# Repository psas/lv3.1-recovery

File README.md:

# LV-3.1 Recovery Repository

The LV-3.1 Electromechanical Recovery System (ERS) is a fully-resettable recovery system for the [PSAS](http://psas.pdx.edu/) Launch Vehicle v 3.1 (LV-3.1). Each ERS "unit" releases a single parachute. The top unit deploys our ballute test parachute that's in the nose cone, the next ERS unit releases a standard drogue, and the final ERS unit releases the main parachute.

## Mechanical CAD
All mechanical CAD has been moved to OnShape and can be found [here](https://cad.onshape.com/documents/03e169a7501c9614bcd8fe34/w/d2206dc55680e29e4d8f6e15/e/43f9d4697ebc459acca1436a).

## Control System

In this Git repo is a PCB with STM32F091 microcontroller that controls the system. See the ControlSystem directory.

## Testing and Analysis

The ERS system will be tested by dropping it from a helicopter over a field. Many parameters must be considered for this test including wind speed, altitude, field size, parachute drag coefficients, and parachute release timing. Analysis of drop test dispersal patterns based on fixing some parameters and simulating variation in others enables us to choose an appropriate drop site and drop parameters. Analysis notebooks can by found in the /analysis directory.

* [Parent Directory](https://github.com/psas/lv3.1-recovery/tree/master/Analysis)
* [Primary mission analysis document](https://github.com/psas/lv3.1-recovery/blob/master/Analysis/Mission_Analysis.ipynb)
* [Jupyter Notebook to run simulations](https://github.com/psas/lv3.1-recovery/blob/master/Analysis/drop_test_simulator.ipynb)

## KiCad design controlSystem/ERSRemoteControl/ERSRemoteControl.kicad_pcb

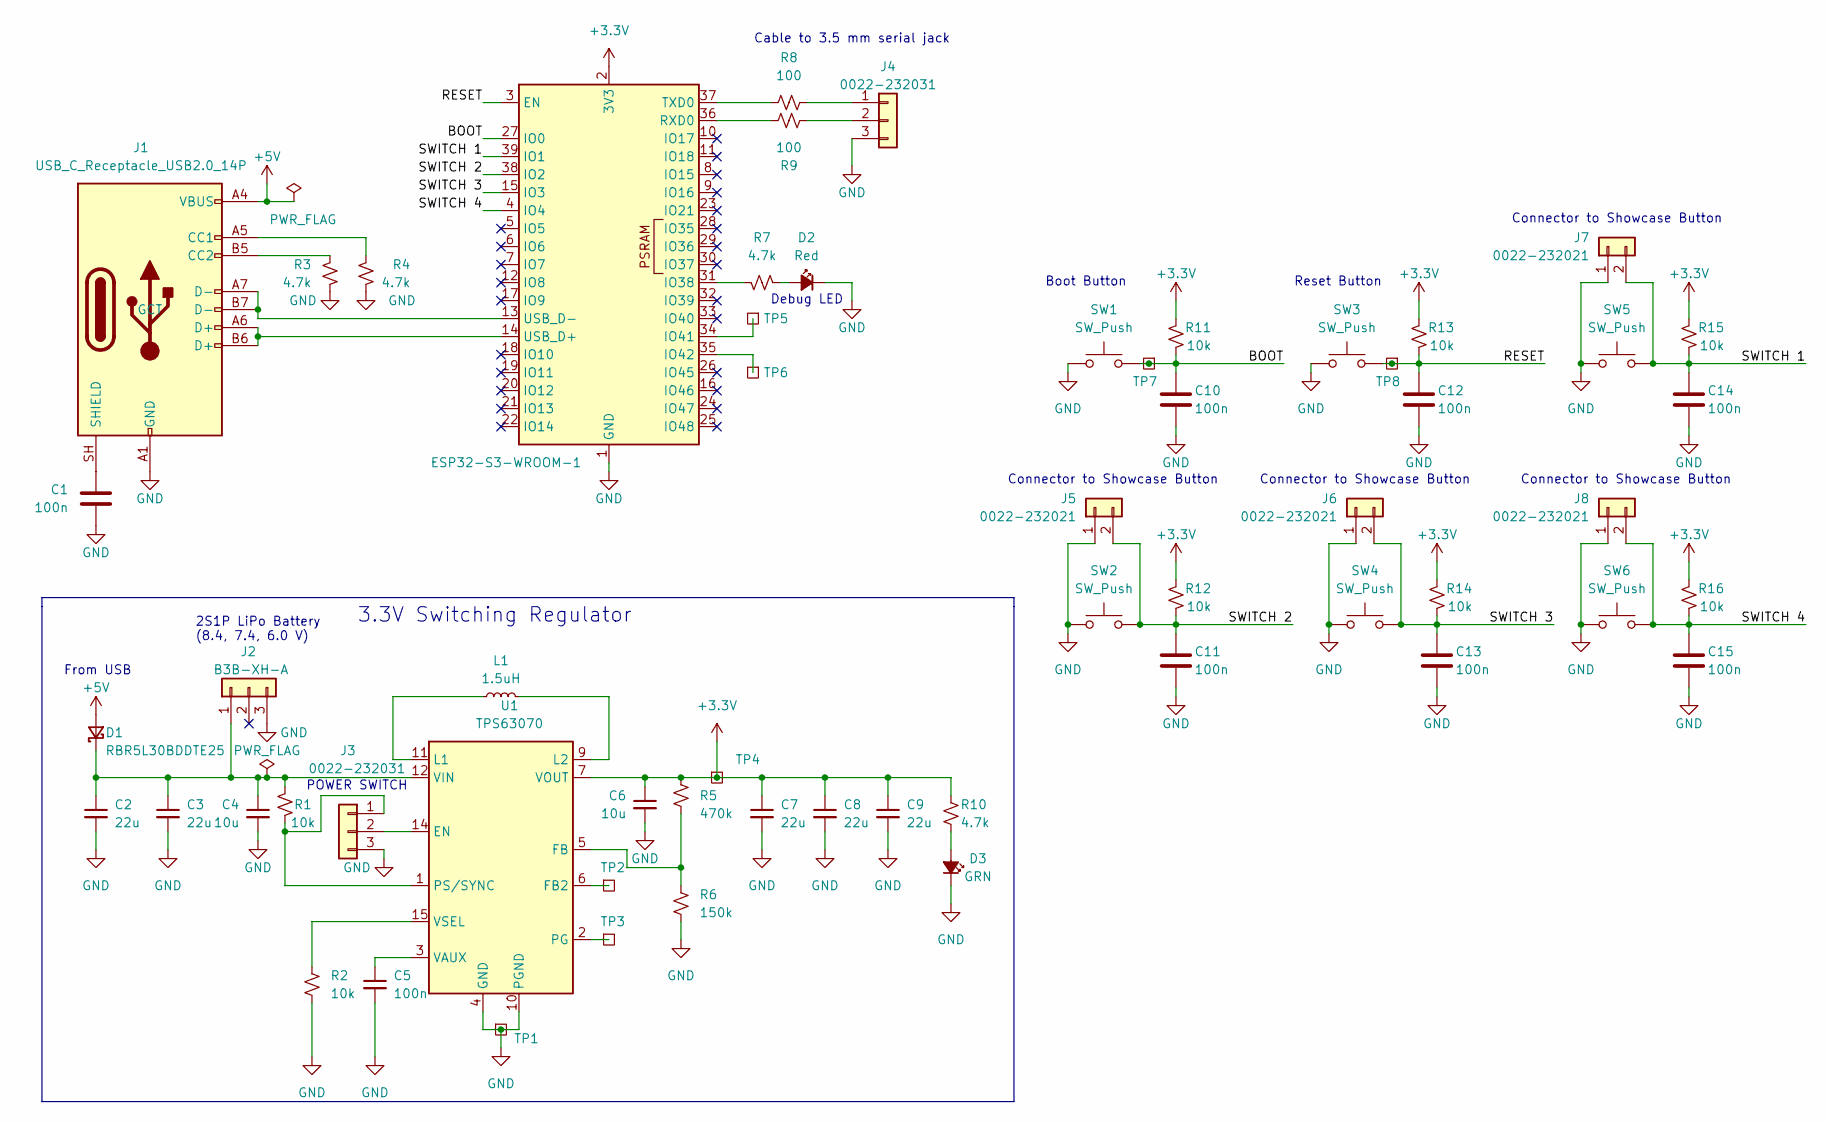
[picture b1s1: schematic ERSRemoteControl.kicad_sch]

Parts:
C1, C5, C10, C11, C12, C13, C14, C15: 100n; C_0603_1608Metric; MPN CL10B104KB8WPNC
C2, C3, C7, C8, C9: 22u; C_0805_2012Metric; MPN GRT21BC81C226ME13L
C4, C6: 10u; C_0805_2012Metric; MPN GRT21BC71E106KE13K
D1: RBR5L30BDDTE25; D_SMA; MPN RBR5L30BDDTE25
D2: Red; LED_0603_1608Metric; MPN 150060SS75000
D3: GRN; LED_0603_1608Metric; MPN 150060GS75000
J1: USB_C_Receptacle_USB2.0_14P; USB_C_Receptacle_Palconn_UTC16-G; MPN USB4105-GF-A
J2: B3B-XH-A; JST_XH_B3B-XH-A_1x03_P2.50mm_Vertical; MPN B3B-XH-A
J3, J4: 0022-232031; Molex_KK-254_AE-6410-03A_1x03_P2.54mm_Vertical; MPN 22232031
J5, J6, J7, J8: 0022-232021; Molex_KK-254_AE-6410-02A_1x02_P2.54mm_Vertical; MPN 22232021
L1: 1.5uH; L_Vishay_IHLP-2020; MPN IHLP2020CZER1R5M11
R1, R2, R11, R12, R13, R14, R15, R16: 10k; R_0603_1608Metric; MPN RC0603FR-0710KL
R3, R4, R7, R10: 4.7k; R_0603_1608Metric; MPN RMCF0603FT4K70
R5: 470k; R_0603_1608Metric; MPN RMCF0603FT470K
R6: 150k; R_0603_1608Metric; MPN RC0603FR-07150KL
R8, R9: 100; R_0603_1608Metric; MPN RC0603FR-07100RL
SW1, SW2, SW3, SW4, SW5, SW6: SW_Push; SW_PUSH_6mm; MPN B3F-1000
TP1, TP2, TP3, TP4, TP5, TP6, TP7, TP8: Test-Point; TP-through-hole-1X01
U1: TPS63070; U-TI-TPS63070; MPN TPS63070RNMR
U2: ESP32-S3-WROOM-1; MPN ESP32-S3-WROOM-1-N4R8

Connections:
+3.3V: C6.1, C7.1, C8.1, C9.1, R5.1, R10.1, R11.1, R12.1, R13.1, R14.1, R15.1, R16.1, TP4.1 (1_1), U1.7 (VOUT), U1.8 (VOUT), U1.TIE2 (VOUT), U2.2 (3V3)
+5V: D1.2 (A), J1.A4 (VBUS), J1.A9 (VBUS), J1.B4 (VBUS), J1.B9 (VBUS)
/BOOT: C10.1, R11.2, SW1.1, TP7.1 (1_1), U2.27 (IO0)
/RESET: C12.1, R13.2, SW3.1, TP8.1 (1_1), U2.3 (EN)
/SWITCH 1: C14.1, J7.2, R15.2, SW5.1, U2.39 (IO1)
/SWITCH 2: C11.1, J5.2, R12.2, SW2.1, U2.38 (IO2)
/SWITCH 3: C13.1, J6.2, R14.2, SW4.1, U2.15 (IO3)
/SWITCH 4: C15.1, J8.2, R16.2, SW6.1, U2.4 (IO4)
GND: C1.2, C2.2, C3.2, C4.2, C5.2, C6.2, C7.2, C8.2, C9.2, C10.2, C11.2, C12.2, C13.2, C14.2, C15.2, D2.1 (K), D3.1 (K), J1.A1 (GND), J1.A12 (GND), J1.B1 (GND), J1.B12 (GND), J2.3, J3.3, J4.3, J5.1, J6.1, J7.1, J8.1, R2.2, R3.2, R4.2, R6.2, SW1.2, SW2.2, SW3.2, SW4.2, SW5.2, SW6.2, TP1.1 (1_1), U1.4 (GND), U1.10 (PGND), U2.1 (GND), U2.40 (GND), U2.41 (GND)
unnamed: C2.1, C3.1, C4.1, D1.1 (K), J2.1, R1.2, U1.12 (VIN), U1.13 (VIN), U1.TIE1 (VIN)
unnamed: D2.2 (A), R7.1
unnamed: D3.2 (A), R10.2
unnamed: J1.A5 (CC1), R4.1
unnamed: J1.B5 (CC2), R3.1
unnamed: C1.1, J1.SH (SHIELD)
unnamed: J3.1, R1.1, U1.1 (PS/SYNC)
unnamed: J3.2, U1.14 (EN)
unnamed: J4.1, R8.2
unnamed: J4.2, R9.1
unnamed: TP2.1 (1_1), U1.6 (FB2)
unnamed: R5.2, R6.1, U1.5 (FB)
unnamed: L1.1, U1.11 (L1)
unnamed: L1.2, U1.9 (L2)
unnamed: TP3.1 (1_1), U1.2 (PG)
unnamed: C5.1, U1.3 (VAUX)
unnamed: R2.1, U1.15 (VSEL)
unnamed: R7.2, U2.31 (IO38)
unnamed: TP5.1 (1_1), U2.34 (IO41)
unnamed: TP6.1 (1_1), U2.35 (IO42)
unnamed: R9.2, U2.36 (RXD0)
unnamed: R8.1, U2.37 (TXD0)
unnamed: J1.A6 (D+), J1.B6 (D+), U2.14 (USB_D+)
unnamed: J1.A7 (D-), J1.B7 (D-), U2.13 (USB_D-)

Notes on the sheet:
Reset Button
3.3V Switching Regulator
2S1P LiPo Battery (8.4, 7.4, 6.0 V)
Connector to Showcase Button
Boot Button
Cable to 3.5 mm serial jack
From USB
POWER SWITCH
Debug LED

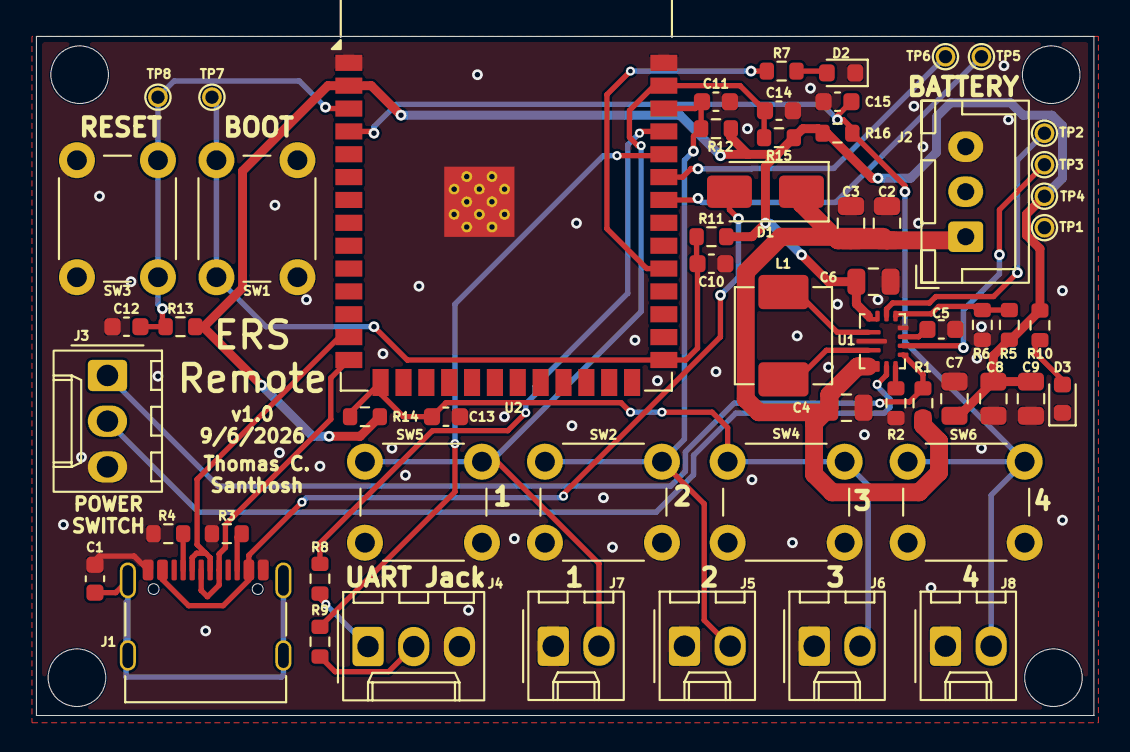
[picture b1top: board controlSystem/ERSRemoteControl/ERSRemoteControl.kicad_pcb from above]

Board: 2 copper layers, 58.8 x 37.7 mm, 59 parts (0 on the bottom side), 33 nets.

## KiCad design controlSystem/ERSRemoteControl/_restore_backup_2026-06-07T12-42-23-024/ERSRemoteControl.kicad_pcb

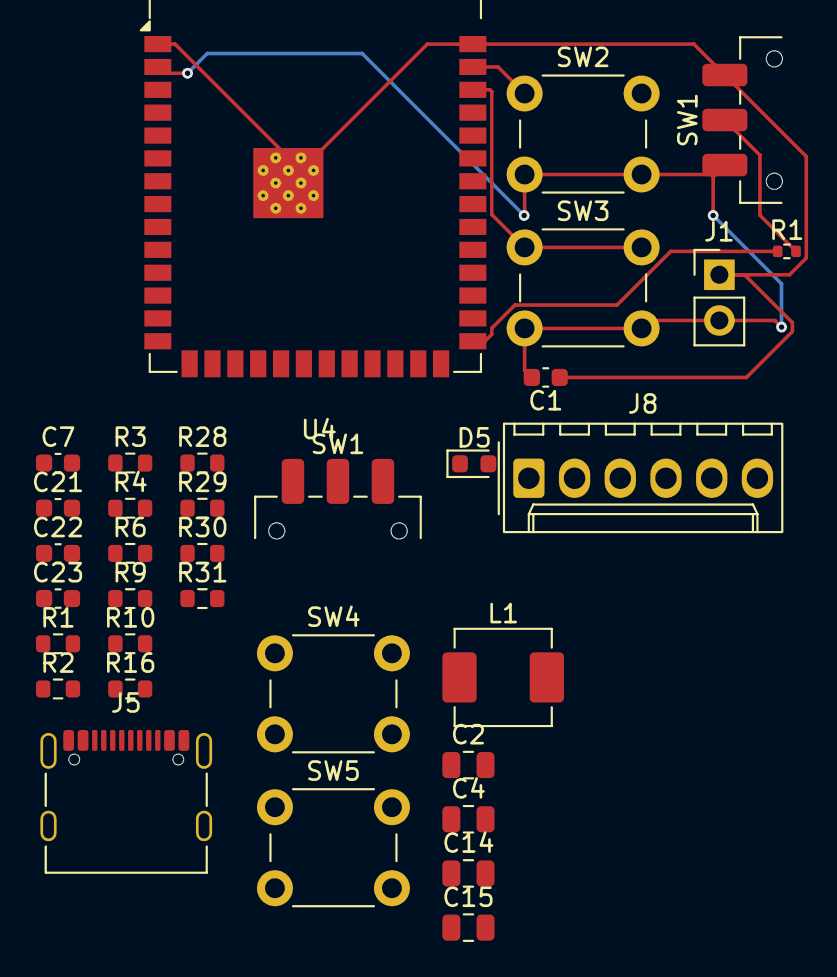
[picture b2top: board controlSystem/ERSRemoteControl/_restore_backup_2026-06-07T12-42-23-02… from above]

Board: 2 copper layers, 34 parts (0 on the bottom side), 17 nets.

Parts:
C1, C7, C21, C22, C23: 100n; C_0603_1608Metric
C2, C4, C14, C15: 22u; C_0805_2012Metric
D5: GRN; LED_0603_1608Metric
J1: Conn_01x02_Socket; PinHeader_1x02_P2.54mm_Vertical
J5: USB_C_Receptacle_USB2.0_14P; USB_C_Receptacle_Palconn_UTC16-G
J8: 00222-32051; Molex_KK-254_AE-6410-06A_1x06_P2.54mm_Vertical
L1: 1.5uH; L_Vishay_IHLP-2020
R1: R_US; R_0402_1005Metric
R1#2, R2, R3: 220; R_0603_1608Metric
R4, R6, R30, R31: 10k; R_0603_1608Metric
R9: 470k; R_0603_1608Metric
R10: 150k; R_0603_1608Metric
R16, R28, R29: 4.7k; R_0603_1608Metric
SW1, SW1#2: SW_SPDT; SW_SPDT_CK_JS102011SAQN
SW2, SW3, SW4, SW5: SW_Push; SW_PUSH_6mm
U4: ESP32-S3-WROOM-1

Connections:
+3.3V: C1.1, C14.1, C15.1, J1.2, R9.1, R16.1, R30.1, R31.1, SW1.1 (A), SW1#2.1 (A), SW2.2, SW3.2, U4.2 (3V3)
+5V: C2.1, C4.1, J5.A4 (VBUS), J5.A9 (VBUS), J5.B4 (VBUS), J5.B9 (VBUS), R6.1
GND: C1.2, C2.2, C4.2, C7.2, C14.2, C15.2, C21.2, C22.2, C23.2, D5.1 (K), J1.1, J5.A1 (GND), J5.A12 (GND), J5.B1 (GND), J5.B12 (GND), R4.2, R10.2, R28.2, R29.2, SW1.3 (C), SW1#2.3 (C), SW4.2, SW5.2, U4.1 (GND), U4.40 (GND), U4.41 (GND)
unnamed: D5.2 (A), R16.2
unnamed: J5.A5 (CC1), R29.1
unnamed: J5.B5 (CC2), R28.1
unnamed: R2.2, SW2.1
unnamed: R3.2, SW3.1
unnamed: R1.2, R1#2.2, SW1.2 (B), SW1#2.2 (B)
unnamed: R9.2, R10.1
unnamed: C22.1, R30.2, SW4.1, U4.3 (EN)
unnamed: C23.1, R1.1, R31.2, SW5.1, U4.27 (IO0)
unnamed: R2.1, U4.39 (IO1)
unnamed: R3.1, U4.38 (IO2)
unnamed: R1#2.1, U4.15 (IO3)
unnamed: J5.A6 (D+), J5.B6 (D+), U4.14 (USB_D+)
unnamed: J5.A7 (D-), J5.B7 (D-), U4.13 (USB_D-)

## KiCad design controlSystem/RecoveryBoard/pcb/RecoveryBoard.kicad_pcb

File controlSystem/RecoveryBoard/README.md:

# Electromechanical Recovery System (ERS) v4.0 Controller Board 

## General information
This board controls the ERS v4 modules in LV3.1 and hopefully eventually in LV4.

Full documentation can be found [here](https://docs.google.com/document/d/1TOoC-d3vpsw2uvtvazEmFV9_g59nFPVRWKC9Ye5qgKw/edit?usp=sharing)

## Firmware

The firmware is written in C and runs on top of ChibiOS, a small RTOS. See the "firmware" directory. The [oresat-firmware](https://github.com/oresat/oresat-firmware) repository has instructions on how to get started on the tool chain.

## License

All materials in this repo are copyright Portland State Aerospace Society and are licensed under the CERN Open Hardware Licence Version 2 -
Strongly Reciprocal (CERN-OHL-S v2), or any later version. A copy of the license is located in [here](LICENSE.md).

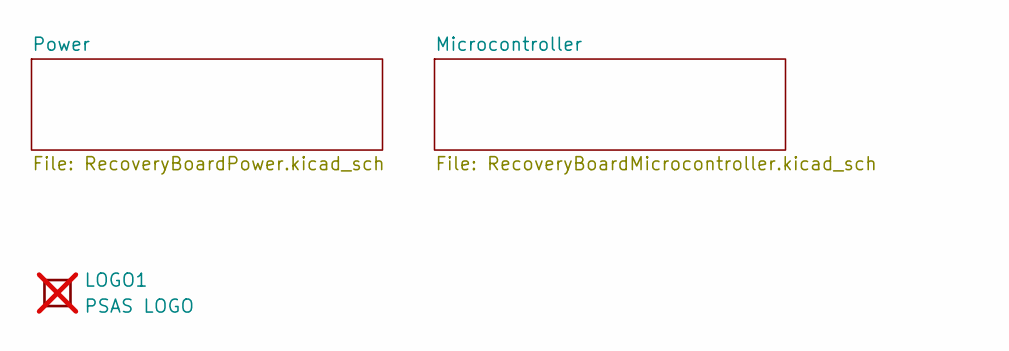
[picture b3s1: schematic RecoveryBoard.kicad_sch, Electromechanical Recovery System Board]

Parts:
LOGO1: PSAS LOGO; PSAS_LOGO_10X10; not fitted

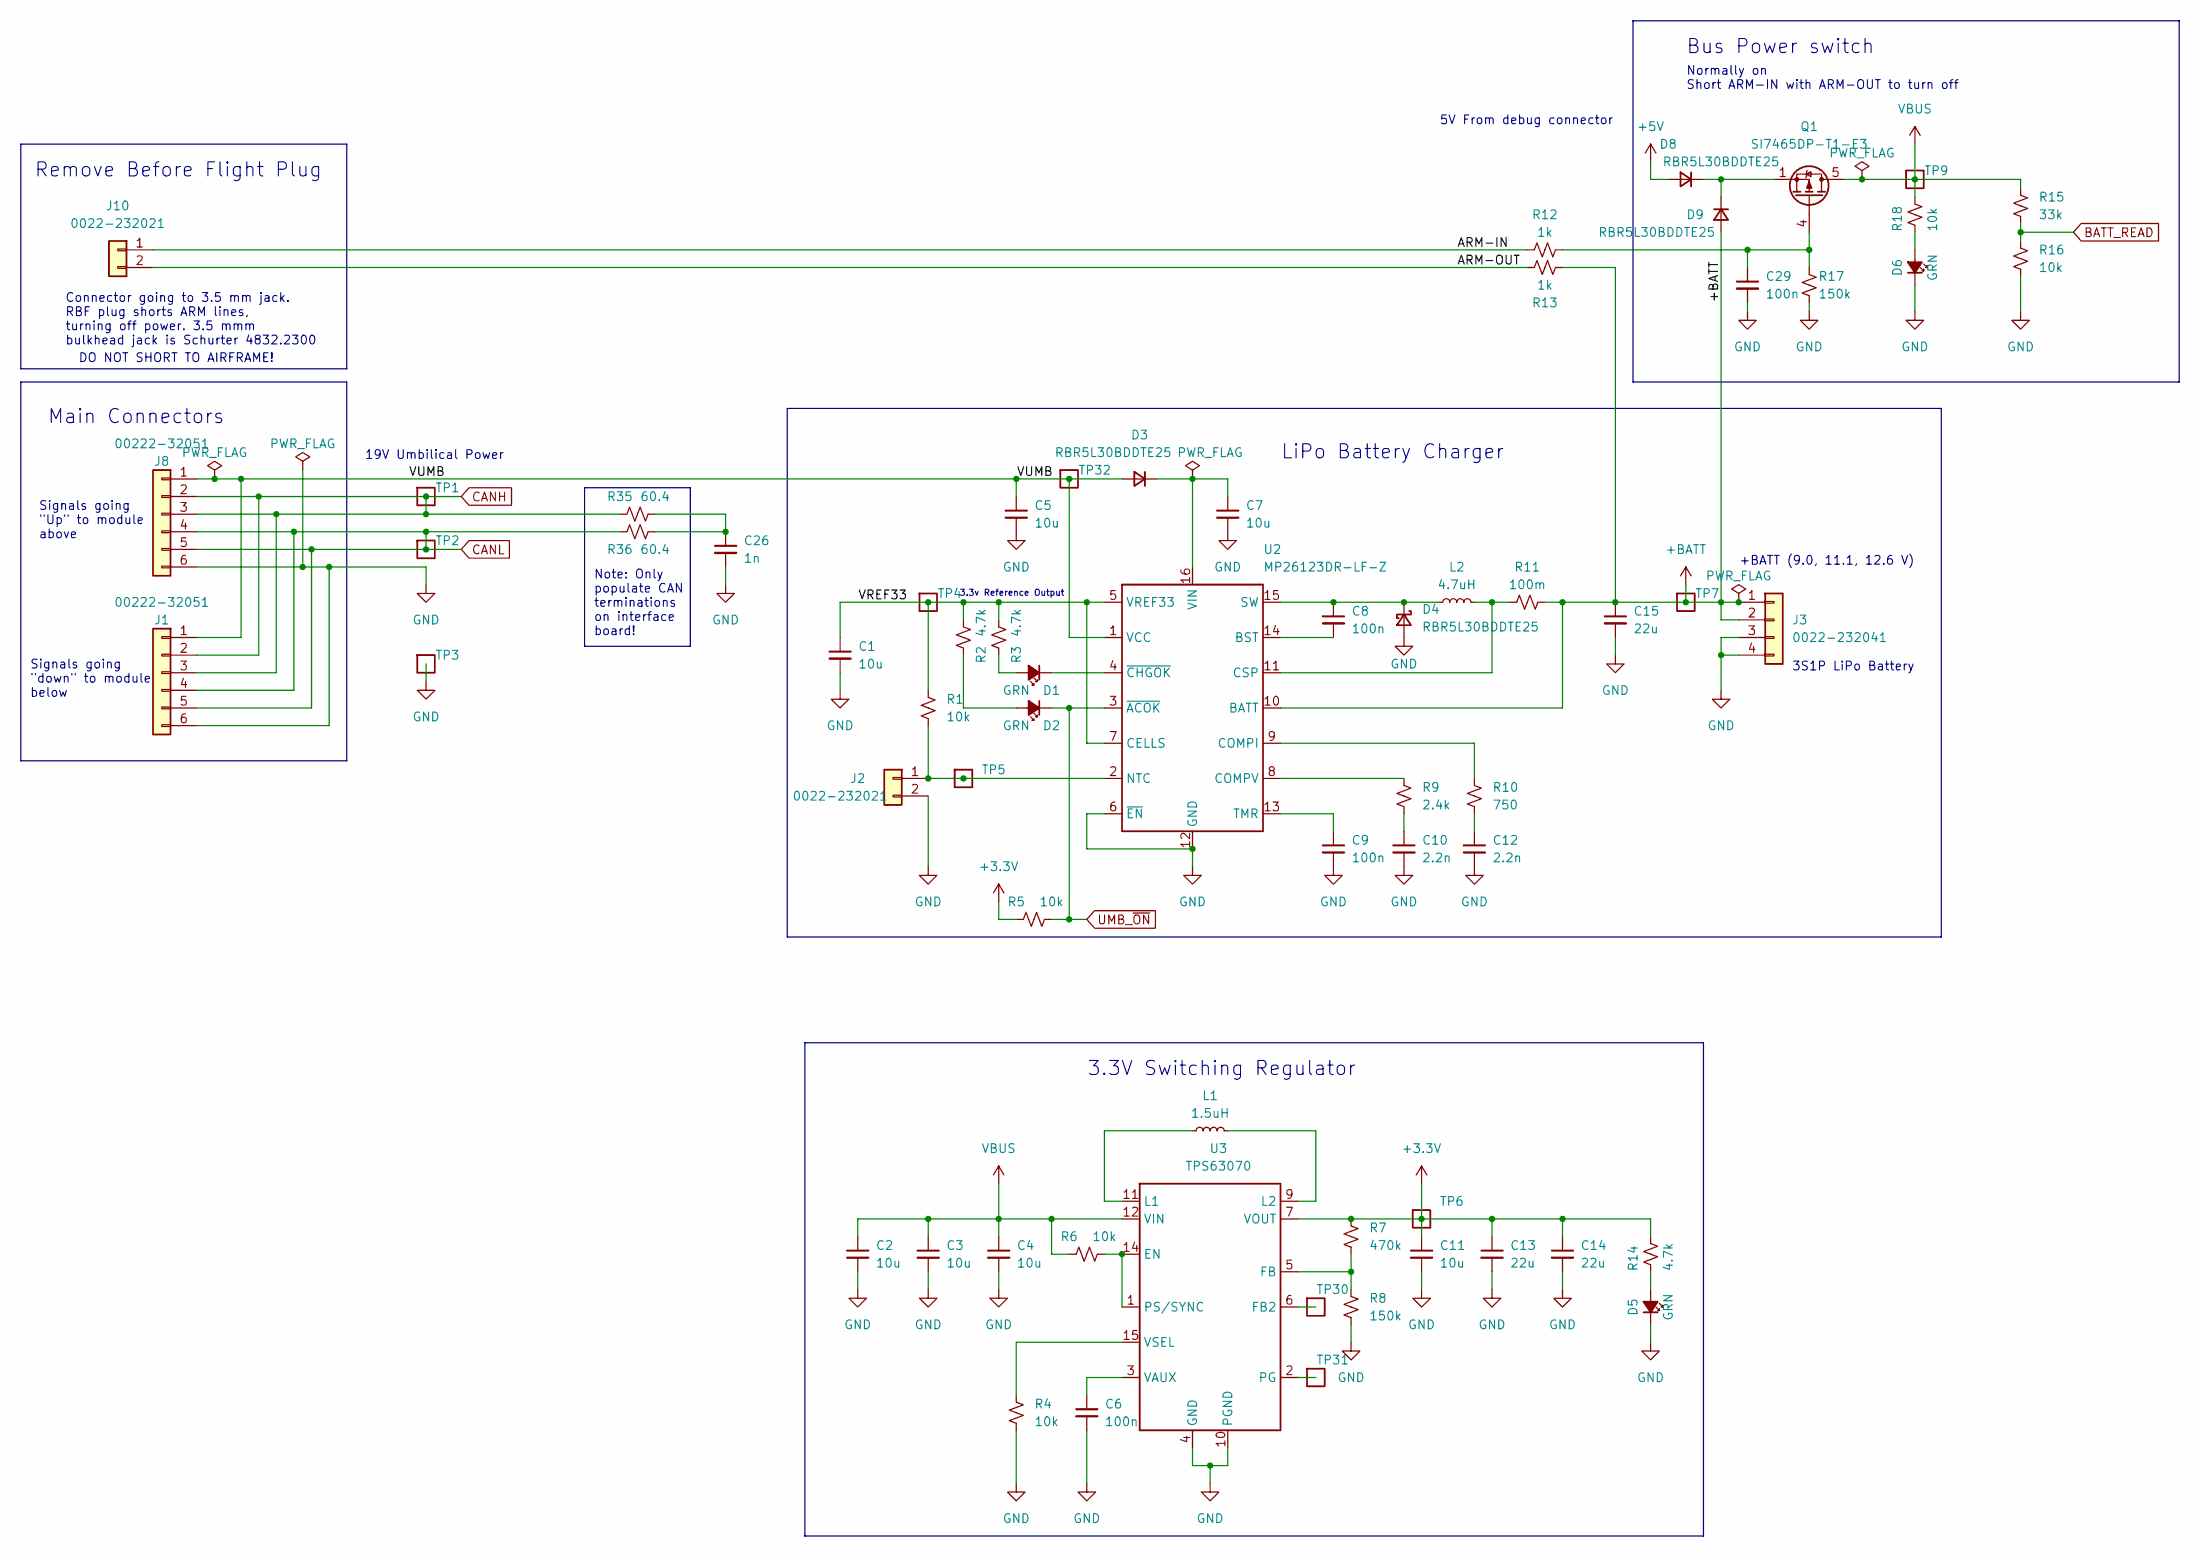
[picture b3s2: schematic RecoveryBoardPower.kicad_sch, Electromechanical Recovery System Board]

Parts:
C1, C2, C3, C5, C7: 10u; C_0805_2012Metric; MPN GRM21BR61H106KE43L
C4, C11: 10u; C_0603_1608Metric; MPN GRT188R61E106ME13D
C6, C8, C9, C29: 100n; C_0603_1608Metric; MPN CL10B104KB8WPNC
C10, C12: 2.2n; C_0603_1608Metric; MPN CL10B222KB8WPNC
C13, C14, C15: 22u; C_0805_2012Metric; MPN GRT21BR61E226ME13L
C26: 1n; C_0603_1608Metric; MPN CL10B102KB85PNL
D1, D2, D5, D6: GRN; LED_0603_1608Metric; MPN 150060GS75000
D3, D4, D8, D9: RBR5L30BDDTE25; D_SMA; MPN RBR5L30BDDTE25
J1, J8: 00222-32051; Molex_KK-254_AE-6410-06A_1x06_P2.54mm_Vertical; MPN 22232061
J2, J10: 0022-232021; Molex_KK-254_AE-6410-02A_1x02_P2.54mm_Vertical; MPN 22232021
J3: 0022-232041; Molex_KK-254_AE-6410-04A_1x04_P2.54mm_Vertical; MPN 22232041
L1: 1.5uH; L_Vishay_IHLP-2020; MPN IHLP2020CZER1R5M11
L2: 4.7uH; L_Vishay_IHLP-2020; MPN IHLP2020BZER4R7M11
Q1: SI7465DP-T1-E3; PowerPAK_SO-8_Single; MPN SI7141DP-T1-GE3
R1, R4, R5, R6, R16, R18: 10k; R_0603_1608Metric; MPN RC0603FR-0710KL
R2, R3, R14: 4.7k; R_0603_1608Metric; MPN RC0603FR-074K7L
R7: 470k; R_0603_1608Metric; MPN RC0603FR-07470KL
R8, R17: 150k; R_0603_1608Metric; MPN RC0603FR-07150KL
R9: 2.4k; R_0603_1608Metric; MPN RC0603FR-072K4L
R10: 750; R_0603_1608Metric; MPN RC0603FR-07750RL
R11: 100m; R_1206_3216Metric; MPN CSR1206FTR100
R12, R13: 1k; R_0603_1608Metric; MPN RC0603FR-071KL
R15: 33k; R_0603_1608Metric; MPN RC0603FR-0733KL
R35, R36: 60.4; R_1206_3216Metric; MPN RC0603FR-0760R4L
TP1, TP2, TP3, TP4, TP5, TP6, TP7, TP9, TP30, TP31, TP32: Test-Point; TP-through-hole-1X01
U2: MP26123DR-LF-Z; QFN-16-1EP_4x4mm_P0.65mm_EP2.5x2.5mm; MPN MP26123DR-LF-Z
U3: TPS63070; U-TI-TPS63070; MPN TPS63070RNMR

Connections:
+3.3V: C11.1, C13.1, C14.1, R5.1, R7.1, R14.1, TP6.1, U3.7 (VOUT), U3.8 (VOUT), U3.TIE2 (VOUT); also elsewhere on the board
+5V: D8.2 (A); also elsewhere on the board
+BATT: C15.1, D9.2 (A), J3.1, J3.2, R11.2, R13.1, TP7.1, U2.10 (BATT)
/Power/ARM-IN: J10.1, R12.1
/Power/ARM-OUT: J10.2, R13.2
/Power/VREF33: C1.1, R1.1, R2.1, R3.1, TP4.1, U2.5 (VREF33), U2.7 (CELLS)
/Power/VUMB: C5.1, D3.2 (A), J1.1, J8.1, TP32.1, U2.1 (VCC)
BATT_READ: R15.2, R16.1; also elsewhere on the board
CANH: J1.2, J1.3, J8.2, J8.3, R35.1, TP1.1; also elsewhere on the board
CANL: J1.4, J1.5, J8.4, J8.5, R36.2, TP2.1; also elsewhere on the board
GND: C1.2, C2.2, C3.2, C4.2, C5.2, C6.2, C7.2, C9.2, C10.2, C11.2, C12.2, C13.2, C14.2, C15.2, C26.2, C29.2, D4.2 (A), D5.1 (K), D6.1 (K), J1.6, J2.2, J3.3, J3.4, J8.6, R4.2, R8.2, R16.2, R17.2, TP3.1, U2.6 (~EN), U2.12 (GND), U2.17 (GND), U3.4 (GND), U3.10 (PGND); also elsewhere on the board
unnamed: C10.1, R9.2
unnamed: C12.1, R10.2
unnamed: C26.1, R35.2, R36.1
unnamed: D1.2 (A), R3.2
unnamed: D1.1 (K), U2.4 (~CHGOK)
unnamed: D2.2 (A), R2.2
unnamed: C7.1, D3.1 (K), U2.16 (VIN)
unnamed: C8.1, D4.1 (K), L2.1, U2.15 (SW)
unnamed: D5.2 (A), R14.2
unnamed: D6.2 (A), R18.2
unnamed: D8.1 (K), D9.1 (K), Q1.1 (S), Q1.2 (S), Q1.3 (S)
unnamed: J2.1, R1.2, TP5.1, U2.2 (NTC)
unnamed: C29.1, Q1.4 (G), R12.2, R17.1
unnamed: C8.2, U2.14 (BST)
unnamed: R10.1, U2.9 (COMPI)
unnamed: R9.1, U2.8 (COMPV)
unnamed: L2.2, R11.1, U2.11 (CSP)
unnamed: C9.1, U2.13 (TMR)
unnamed: R6.2, U3.1 (PS/SYNC), U3.14 (EN)
unnamed: TP30.1, U3.6 (FB2)
unnamed: R7.2, R8.1, U3.5 (FB)
unnamed: L1.1, U3.11 (L1)
unnamed: L1.2, U3.9 (L2)
unnamed: TP31.1, U3.2 (PG)
unnamed: C6.1, U3.3 (VAUX)
unnamed: R4.1, U3.15 (VSEL)
UMB_~ON: D2.1 (K), R5.2, U2.3 (~ACOK); also elsewhere on the board
VBUS: C2.1, C3.1, C4.1, Q1.5 (D), R6.1, R15.1, R18.1, TP9.1, U3.12 (VIN), U3.13 (VIN), U3.TIE1 (VIN); also elsewhere on the board

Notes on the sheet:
3.3v Reference Output
Remove Before Flight Plug
3.3V Switching Regulator
Note: Only populate CAN terminations on interface board!
19V Umbilical Power
Bus Power switch
DO NOT SHORT TO AIRFRAME!
3S1P LiPo Battery
5V From debug connector
+BATT (9.0, 11.1, 12.6 V)
Signals going "Up" to module above
Normally on Short ARM-IN with ARM-OUT to turn off
Main Connectors
Connector going to 3.5 mm jack. RBF plug shorts ARM lines, turning off power. 3.5 mmm bulkhead jack is Schurter 4832.2300
Signals going "down" to module below
LiPo Battery Charger

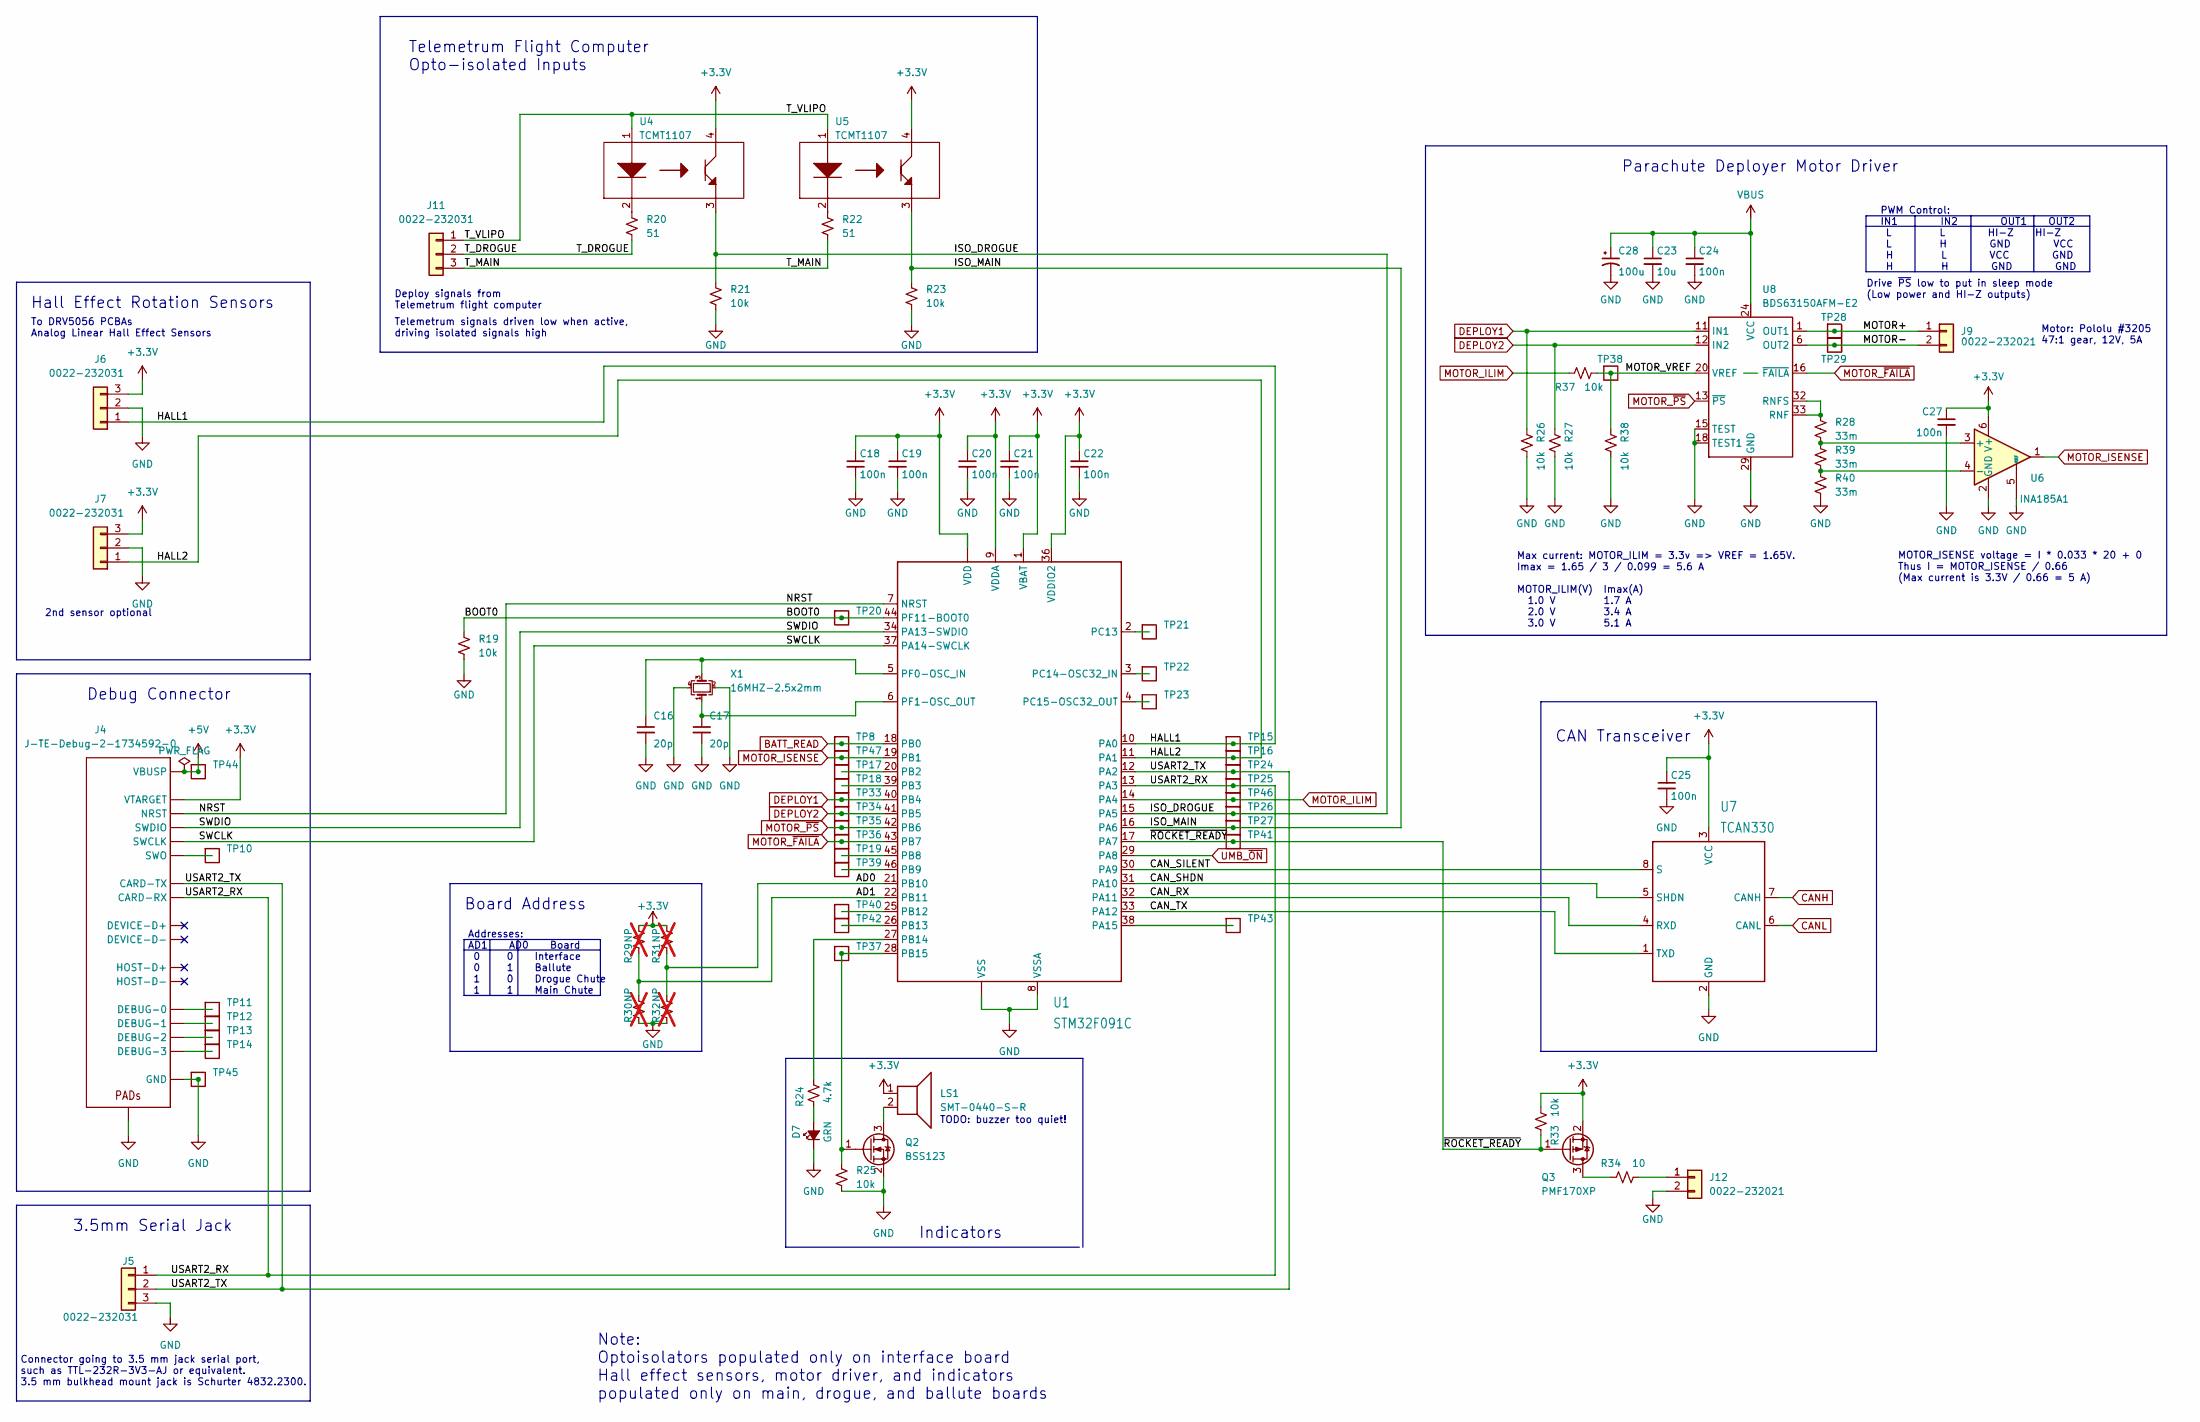
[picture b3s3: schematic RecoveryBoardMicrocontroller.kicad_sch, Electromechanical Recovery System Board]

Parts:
C16, C17: 20p; C_0603_1608Metric; MPN C0603C200G4HAC7867
C18, C19, C20, C21, C22, C24, C25, C27: 100n; C_0603_1608Metric; MPN CL10B104KB8WPNC
C23: 10u; C_0805_2012Metric; MPN GRM21BR61H106KE43L
C28: 100u; CP_EIA-7343-43_Kemet-X; MPN T491X107K020AT
D7: GRN; LED_0603_1608Metric; MPN 150060GS75000
J4: J-TE-Debug-2-1734592-0; J-TE_2-1734592-0; MPN 2-1734592-0
J5, J6, J7, J11: 0022-232031; Molex_KK-254_AE-6410-03A_1x03_P2.54mm_Vertical; MPN 22232031
J9, J12: 0022-232021; Molex_KK-254_AE-6410-02A_1x02_P2.54mm_Vertical; MPN 22232021
LS1: SMT-0440-S-R; MPN SMT-0440-S-R
Q2: BSS123; SOT-23; MPN BSS123
Q3: PMF170XP; SOT-323_SC-70; MPN PMF170XP,115
R19, R21, R23, R25, R26, R27, R33, R37, R38: 10k; R_0603_1608Metric; MPN RC0603FR-0710KL
R20, R22: 51; R_0603_1608Metric; MPN RC0603FR-0751RL
R24: 4.7k; R_0603_1608Metric; MPN RC0603FR-074K7L
R28, R39, R40: 33m; R_1206_3216Metric; MPN RLP73M2BR033FTDF
R29, R30, R31, R32: NP; R_0603_1608Metric; not fitted
R34: 10; R_0603_1608Metric; MPN RC0603FR-0710RL
TP8, TP10, TP11, TP12, TP13, TP14, TP15, TP16, TP17, TP18, TP19, TP20, TP21, TP22, TP23, TP24, TP25, TP26, TP27, TP28, TP29, TP33, TP34, TP35, TP36, TP37, TP38, TP39, TP40, TP41, TP42, TP43, TP44, TP45, TP46, TP47: Test-Point; TP-through-hole-1X01
U1: STM32F091C; LQFP-48_7x7mm_P0.5mm; MPN STM32F091CCT7
U4, U5: TCMT1107; SOP-4_4.4x2.6mm_P1.27mm; MPN TCMT1107
U6: INA185A1; SOT-563; MPN INA185A1IDRLR
U7: TCAN330; SOT23-8; MPN TCAN330GDCNT
U8: BDS63150AFM-E2; U-BD63150AFM; MPN BD63150AFM-E2
X1: 16MHZ-2.5x2mm; Crystal_SMD_2520-4Pin_2.5x2.0mm; MPN ECS-160-10-36Q-ES-TR

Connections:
+3.3V: C18.1, C19.1, C20.1, C21.1, C22.1, C25.1, C27.1, J4.11 (VTARGET), J6.3, J7.3, LS1.1, Q3.2 (S), R29.1, R31.1, R33.2, U1.1 (VBAT), U1.9 (VDDA), U1.24 (VDD), U1.36 (VDDIO2), U1.48 (VDD), U4.4 (IN), U5.4 (IN), U6.6 (V+), U7.3 (VCC); also elsewhere on the board
+5V: J4.1 (VBUSP), J4.2 (VBUSP), TP44.1; also elsewhere on the board
/Microcontroller/AD0: R31.2, R32.1, U1.21 (PB10)
/Microcontroller/AD1: R29.2, R30.1, U1.22 (PB11)
/Microcontroller/BOOT0: R19.1, TP20.1, U1.44 (PF11-BOOT0)
/Microcontroller/CAN_RX: U1.32 (PA11), U7.4 (RXD)
/Microcontroller/CAN_SHDN: U1.31 (PA10), U7.5 (SHDN)
/Microcontroller/CAN_SILENT: U1.30 (PA9), U7.8 (S)
/Microcontroller/CAN_TX: U1.33 (PA12), U7.1 (TXD)
/Microcontroller/HALL1: J6.1, TP15.1, U1.10 (PA0)
/Microcontroller/HALL2: J7.1, TP16.1, U1.11 (PA1)
/Microcontroller/ISO_DROGUE: R21.1, TP26.1, U1.15 (PA5), U4.3 (OUT)
/Microcontroller/ISO_MAIN: R23.1, TP27.1, U1.16 (PA6), U5.3 (OUT)
/Microcontroller/MOTOR+: J9.1, TP28.1, U8.1 (OUT1), U8.2 (OUT1), U8.3 (OUT1)
/Microcontroller/MOTOR-: J9.2, TP29.1, U8.6 (OUT2), U8.7 (OUT2), U8.8 (OUT2)
/Microcontroller/MOTOR_VREF: R37.2, R38.1, TP38.1, U8.20 (VREF)
/Microcontroller/NRST: J4.10 (NRST), U1.7 (NRST)
/Microcontroller/SWCLK: J4.15 (SWCLK), U1.37 (PA14-SWCLK)
/Microcontroller/SWDIO: J4.14 (SWDIO), U1.34 (PA13-SWDIO)
/Microcontroller/T_DROGUE: J11.2, R20.2
/Microcontroller/T_MAIN: J11.3, R22.2
/Microcontroller/T_VLIPO: J11.1, U4.1 (A), U5.1 (A)
/Microcontroller/USART2_RX: J4.12 (CARD-RX), J5.1, TP25.1, U1.13 (PA3)
/Microcontroller/USART2_TX: J4.13 (CARD-TX), J5.2, TP24.1, U1.12 (PA2)
/Microcontroller/~ROCKET_READY: Q3.1 (G), R33.1, TP41.1, U1.17 (PA7)
BATT_READ: TP8.1, U1.18 (PB0); also elsewhere on the board
CANH: U7.7 (CANH); also elsewhere on the board
CANL: U7.6 (CANL); also elsewhere on the board
DEPLOY1: R26.1, TP33.1, U1.40 (PB4), U8.11 (IN1)
DEPLOY2: R27.1, TP34.1, U1.41 (PB5), U8.12 (IN2)
GND: C16.2, C17.2, C18.2, C19.2, C20.2, C21.2, C22.2, C23.2, C24.2, C25.2, C27.2, C28.2, D7.1 (K), J4.3 (GND), J4.6 (GND), J4.9 (GND), J4.PAD1 (PAD), J4.PAD2 (PAD), J5.3, J6.2, J7.2, J12.2, Q2.2 (S), R19.2, R21.2, R23.2, R25.2, R26.2, R27.2, R30.2, R32.2, R38.2, R40.2, TP45.1, U1.8 (VSSA), U1.23 (VSS), U1.35 (VSS), U1.47 (VSS), U6.2 (GND), U6.5 (REF), U7.2 (GND), U8.15 (TEST), U8.18 (TEST1), U8.22 (GND), U8.29 (GND), U8.37 (GND), U8.38 (GND), X1.2, X1.4; also elsewhere on the board
MOTOR_ILIM: R37.1, TP46.1, U1.14 (PA4)
MOTOR_ISENSE: TP47.1, U1.19 (PB1), U6.1
MOTOR_~FAILA: TP36.1, U1.43 (PB7), U8.16 (~FAILA)
MOTOR_~PS: TP35.1, U1.42 (PB6), U8.13 (~PS)
unnamed: D7.2 (A), R24.2
unnamed: J4.17 (DEBUG-0), TP11.1
unnamed: J4.18 (DEBUG-1), TP12.1
unnamed: J4.19 (DEBUG-2), TP13.1
unnamed: J4.20 (DEBUG-3), TP14.1
unnamed: J4.16 (SWO), TP10.1
unnamed: J12.1, R34.2
unnamed: LS1.2, Q2.3 (D)
unnamed: Q2.1 (G), R25.1, TP37.1, U1.28 (PB15)
unnamed: Q3.3 (D), R34.1
unnamed: TP43.1, U1.38 (PA15)
unnamed: TP17.1, U1.20 (PB2)
unnamed: TP18.1, U1.39 (PB3)
unnamed: TP19.1, U1.45 (PB8)
unnamed: TP39.1, U1.46 (PB9)
unnamed: TP40.1, U1.25 (PB12)
unnamed: TP42.1, U1.26 (PB13)
unnamed: R24.1, U1.27 (PB14)
unnamed: TP21.1, U1.2 (PC13)
unnamed: TP22.1, U1.3 (PC14-OSC32_IN)
unnamed: TP23.1, U1.4 (PC15-OSC32_OUT)
unnamed: C16.1, U1.5 (PF0-OSC_IN), X1.3
unnamed: C17.1, U1.6 (PF1-OSC_OUT), X1.1
unnamed: R20.1, U4.2 (K)
unnamed: R22.1, U5.2 (K)
unnamed: R28.2, R39.1, U6.3 (+)
unnamed: R39.2, R40.1, U6.4 (-)
unnamed: R28.1, U8.32 (RNFS), U8.33 (RNF), U8.34 (RNF), U8.35 (RNF)
UMB_~ON: U1.29 (PA8); also elsewhere on the board
VBUS: C23.1, C24.1, C28.1, U8.24 (VCC), U8.25 (VCC), U8.26 (VCC); also elsewhere on the board

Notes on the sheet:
2nd sensor optional
Drive ~{PS} low to put in sleep mode (Low power and HI-Z outputs)
To DRV5056 PCBAs Analog Linear Hall Effect Sensors
Connector going to 3.5 mm jack serial port, such as TTL-232R-3V3-AJ or equivalent. 3.5 mm bulkhead mount jack is Schurter 4832.2300.
Deploy signals from Telemetrum flight computer
3.5mm Serial Jack
TODO: buzzer too quiet!
Motor: Pololu #3205 47:1 gear, 12V, 5A
Hall Effect Rotation Sensors
Board Address
PWM Control: IN1 IN2 OUT1 OUT2 L L HI-Z HI-Z L H GND VCC H L VCC GND H H GND GND
Note: Optoisolators populated only on interface board Hall effect sensors, motor driver, and indicators populated only on main, drogue, and ballute boards
Telemetrum Flight Computer Opto-isolated Inputs
Indicators
Debug Connector
MOTOR_ISENSE voltage = I * 0.033 * 20 + 0 Thus I = MOTOR_ISENSE / 0.66 (Max current is 3.3V / 0.66 = 5 A)
Addresses: AD1 AD0 Board 0 0 Interface 0 1 Ballute 1 0 Drogue Chute 1 1 Main Chute
Parachute Deployer Motor Driver
Telemetrum signals driven low when active, driving isolated signals high
Max current: MOTOR_ILIM = 3.3v => VREF = 1.65V. Imax = 1.65 / 3 / 0.099 = 5.6 A MOTOR_ILIM(V) Imax(A) 1.0 V 1.7 A 2.0 V 3.4 A 3.0 V 5.1 A
CAN Transceiver

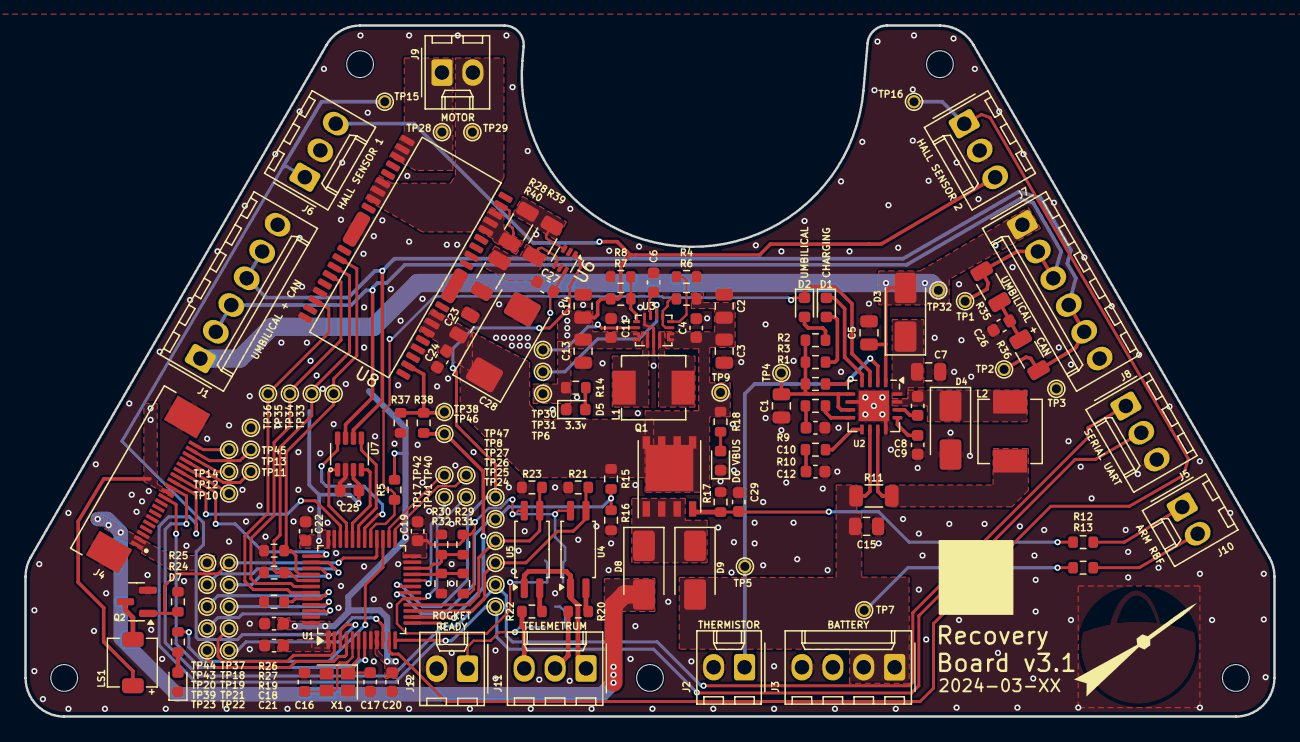
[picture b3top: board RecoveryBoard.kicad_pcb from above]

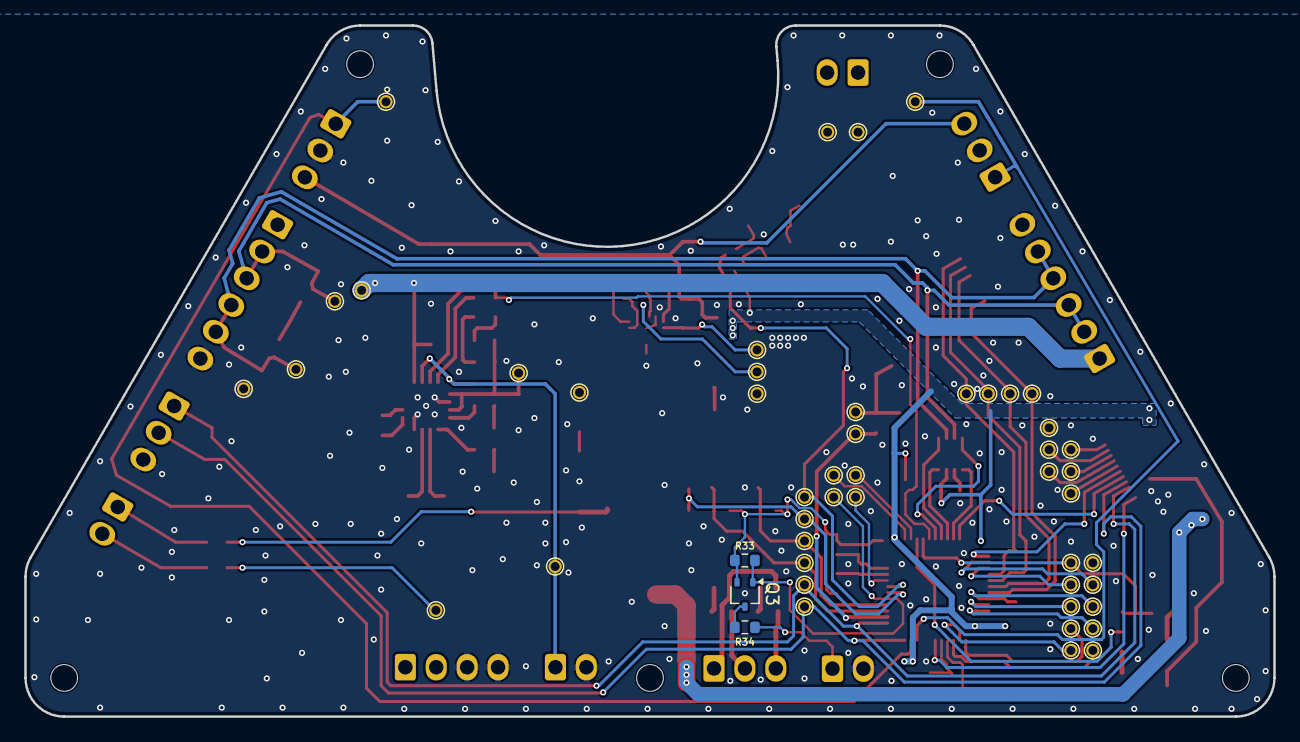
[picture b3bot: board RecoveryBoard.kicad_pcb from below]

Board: 2 copper layers, 102.7 x 56.8 mm, 153 parts (3 on the bottom side), 96 nets.

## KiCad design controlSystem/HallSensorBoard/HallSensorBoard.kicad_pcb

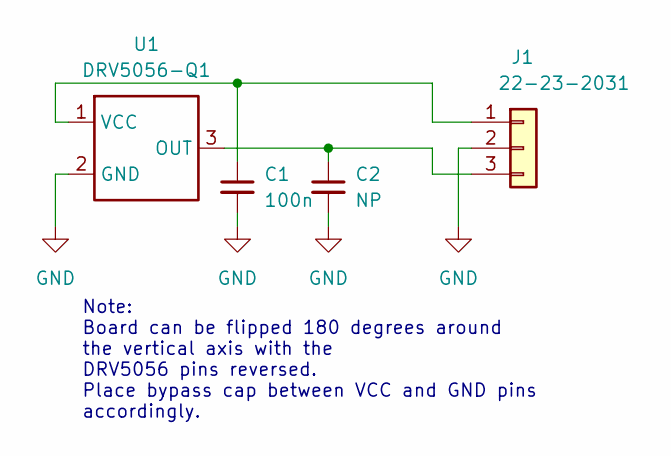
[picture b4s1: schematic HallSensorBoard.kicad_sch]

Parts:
C1: 100n; C_0603_1608Metric
C2: NP; C_0603_1608Metric
J1: 22-23-2031; U-TI-22-23-2031
U1: DRV5056-Q1; TO-92Flat

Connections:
GND: C1.2, C2.2, J1.2, U1.2 (GND)
unnamed: C1.1, J1.1, U1.1 (VCC)
unnamed: C2.1, J1.3, U1.3 (OUT)

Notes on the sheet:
Note: Board can be flipped 180 degrees around the vertical axis with the DRV5056 pins reversed. Place bypass cap between VCC and GND pins accordingly.
